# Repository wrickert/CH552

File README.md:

# CH552
This is a CH552 Devboard and repo for a new pcb buisness card.<br>

* Projects included in this repo
	* CH552 devboard
	
	* Business Card, Type 2
	
	* Plastic Frog

### Dev Board Information ###
Buttons can be sourced here - https://www.aliexpress.com/item/50pcs-lot-SMT-3X6X3-5MM-2PIN-Tactile-Tact-Push-Button-Micro-Switch-G71-Momentary-Free-Shipping/32668690358.html<br>
USB port can be sourced here - https://lcsc.com/product-detail/USB-Connectors_Jing-Extension-of-the-Electronic-Co-LCSC-micro-5PAll-posts-are-not-guided-Flat-welding-High-temperature_C77238.html<br>
Finally, the CH552 can be sourced here - https://lcsc.com/product-detail/USB_CH552G_C111292.html<br>

### Business Card Information ###
In development, I have not even started the software. This is open source hardware like all of my designs.

### Plastic Frog ###
Rubber Ducky knockoff. I have sourced USB swivel drive cases. It is surprising how hard that was to find. Trivial to buy with the usb board, and its easy to find just the usb pcb but hard to find the case. Should cost $0.99 to build.

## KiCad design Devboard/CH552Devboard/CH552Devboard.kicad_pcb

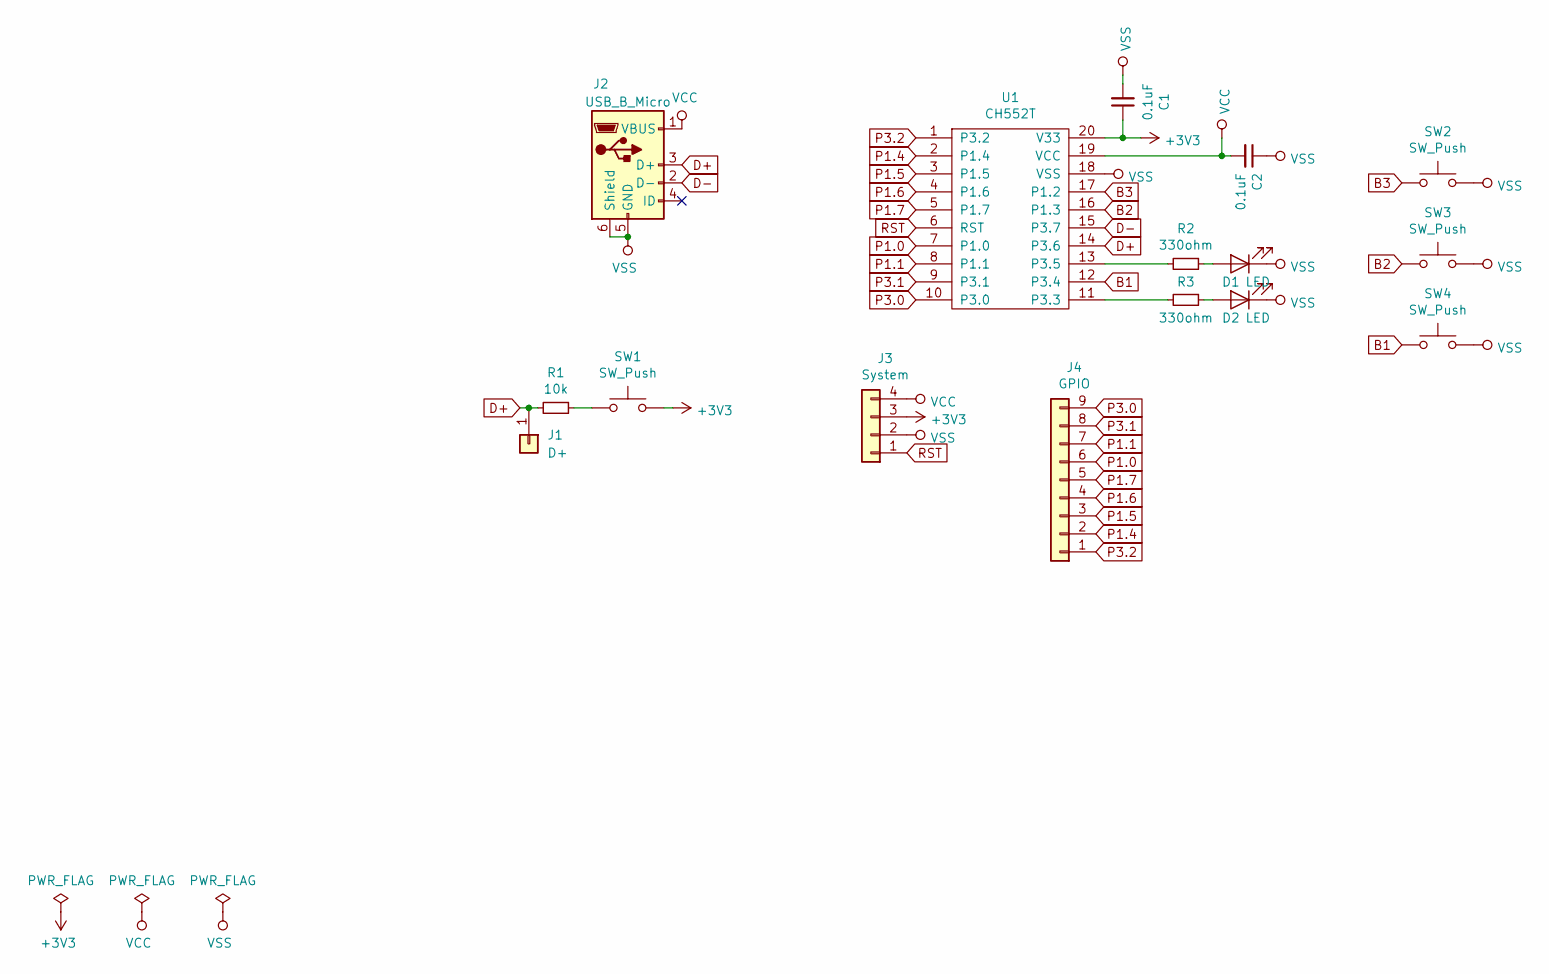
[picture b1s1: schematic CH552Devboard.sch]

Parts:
C1, C2: 0.1uF; C_0805
D1, D2: LED; LED_0805
J1: D+; Pin_Header_Straight_1x01_Pitch1.27mm
J2: USB_B_Micro; USB_Micro-B_Jing
J3: System; Pin_Header_Straight_1x04_Pitch2.54mm
J4: GPIO; Pin_Header_Straight_1x09_Pitch2.54mm
R1: 10k; R_0805
R2, R3: 330ohm; R_0805
SW1, SW2, SW3, SW4: SW_Push; Ali_button
U1: CH552T; TSSOP-20_4.4x6.5mm_Pitch0.65mm

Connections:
+3V3: C1.1, J3.3, SW1.2, U1.20 (V33); also elsewhere on the board
B1: SW4.1, U1.12 (P3.4)
B2: SW3.1, U1.16 (P1.3)
B3: SW2.1, U1.17 (P1.2)
D+: J1.1, J2.3 (D+), R1.2, U1.14 (P3.6)
D-: J2.2 (D-), U1.15 (P3.7)
unnamed: D1.2 (A), R2.1
unnamed: D2.2 (A), R3.1
unnamed 9: R1.1, SW1.1; also elsewhere on the board
unnamed: R2.2, U1.13 (P3.5)
unnamed: R3.2, U1.11 (P3.3)
P1.0: J4.6, U1.7 (P1.0)
P1.1: J4.7, U1.8 (P1.1)
P1.4: J4.2, U1.2 (P1.4)
P1.5: J4.3, U1.3 (P1.5)
P1.6: J4.4, U1.4 (P1.6)
P1.7: J4.5, U1.5 (P1.7)
P3.0: J4.9, U1.10 (P3.0)
P3.1: J4.8, U1.9 (P3.1)
P3.2: J4.1, U1.1 (P3.2)
RST: J3.1, U1.6 (RST)
VCC: C2.2, J2.1 (VBUS), J3.4, U1.19 (VCC)
VSS: C1.2, C2.1, D1.1 (K), D2.1 (K), J2.5 (GND), J2.6 (Shield), J3.2, SW2.2, SW3.2, SW4.2, U1.18 (VSS)

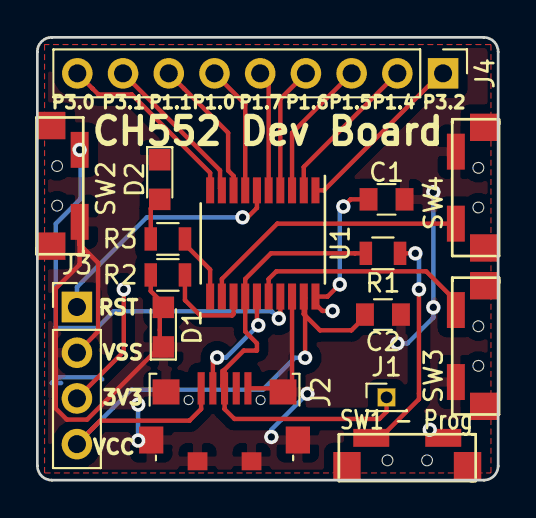
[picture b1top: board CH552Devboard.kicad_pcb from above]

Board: 2 copper layers, 25.6 x 24.6 mm, 16 parts (0 on the bottom side), 23 nets.

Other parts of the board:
SW1 - Prog: SW_Push; Ali_button

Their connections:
+3V3: SW1 - Prog.2; also elsewhere on the board
unnamed 9: SW1 - Prog.1; also elsewhere on the board

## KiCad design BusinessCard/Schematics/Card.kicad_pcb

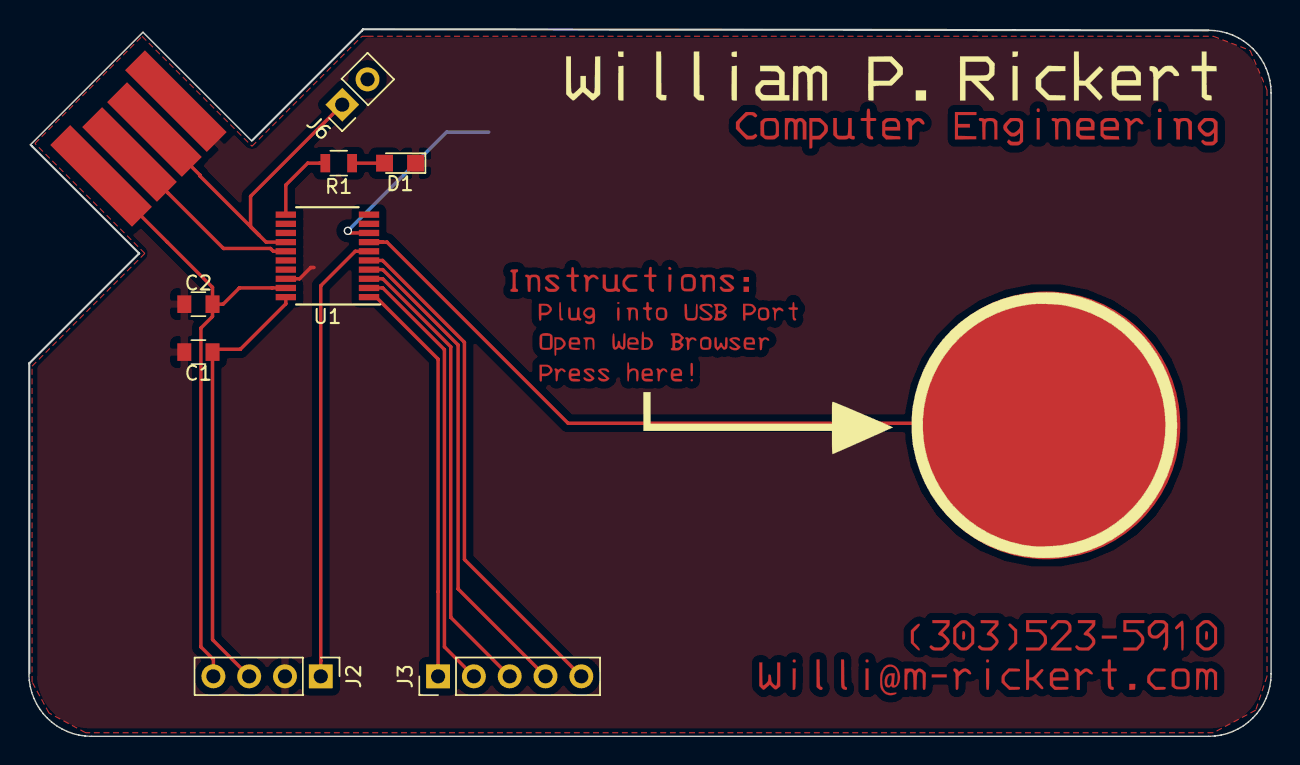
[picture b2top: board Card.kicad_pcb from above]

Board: 2 copper layers, 88.1 x 50.2 mm, 11 parts (1 on the bottom side), 14 nets.

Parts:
C1, C2: 0.1uF; C_0805
D1: LED; LED_0805
J1: USB_A; USBPCB
J2: System; Pin_Header_Straight_1x04_Pitch2.54mm
J3: ExpansionPort; Pin_Header_Straight_1x05_Pitch2.54mm
J4: CapPad1
J5: CapPad2
J6: Programming Port; Pin_Header_Straight_1x02_Pitch2.54mm
R1: 330ohm; R_0805
U1: CH552T; TSSOP-20_4.4x6.5mm_Pitch0.65mm

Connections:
+3V3: C1.1, J2.3, J6.2, U1.20
Cap_button2: J5.1, U1.8
D+: J1.3, J6.1, U1.14
D-: J1.2, U1.15
unnamed: D1.2, R1.1
unnamed: R1.2, U1.11
P1.4: J3.2, U1.2
P1.5: J3.3, U1.3
P1.6: J3.4, U1.4
P1.7: J3.5, U1.5
P3.2: J3.1, U1.1
RST: J2.1, U1.6
VCC: C2.2, J1.1, J2.4, U1.19
VSS: C1.2, C2.1, D1.1, J1.4, J2.2, U1.18

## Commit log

2019-02-20 Ordered v1 dev board
2019-03-06 Recieved V1, fixed issue. Seems to work now.
2019-03-06 Cleaned up, added to readme
2019-03-06 Added silkscreen to devboard
2019-03-06 Updated zip to v2
2019-03-07 Finished and ordered PlasticFrog v1
2019-03-08 Cleaned up card schematics
2019-03-25 Cant believe I had D+ and D- mixed...
2019-04-12 Updated information
2019-05-07 Updated footprint
